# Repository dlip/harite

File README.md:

# Harite 5-way Switch Keyboard

> Harite v2 now released! <https://github.com/dlip/harite-v2>

- 5-way switches - SKRHADE010 rated at 1,000,000 cycles for each direction
- RP2040-Zero controller
- Split using USB-C to connect the halves
- Dual Cirque 40mm trackpads (optional - you can put a Ploopy or other small trackball in place instead)
- QMK Firmware
- Custom PCB and case
- Hot-swapable joystick caps
- The name comes from the Sumo Slap attack in Japanese
- See a [video demonstration](https://youtu.be/vVsztPqckJc)
- If you would like to make your own, checkout the detailed [build guide](build.md)

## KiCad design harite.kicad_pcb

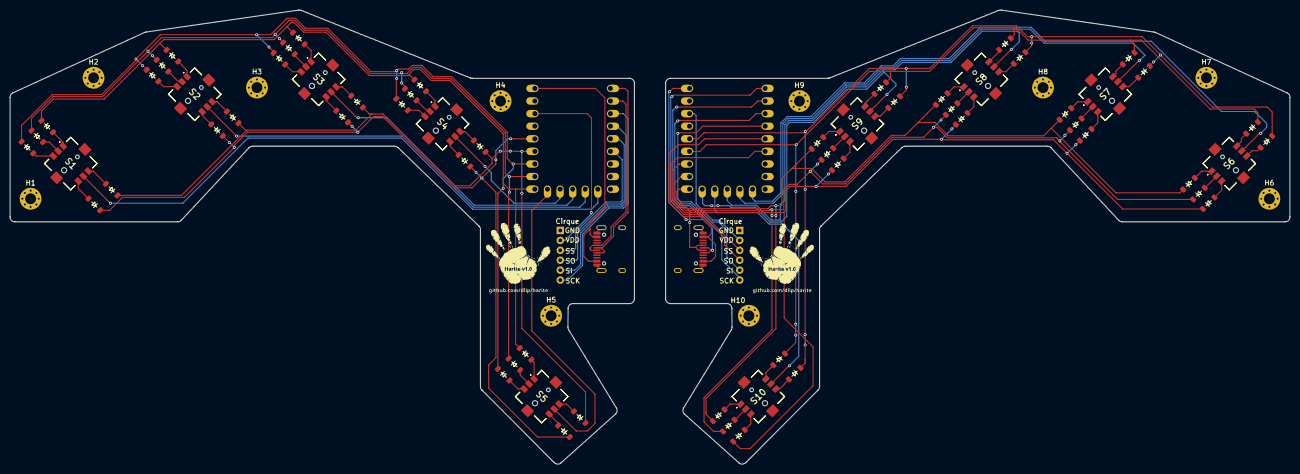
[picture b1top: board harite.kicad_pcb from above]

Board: 2 copper layers, 258.2 x 91.6 mm, 76 parts (0 on the bottom side), 88 nets.

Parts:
D1, D2, D3, D4, D5, D6, D7, D8, D9, D10, D11, D12, D13, D14, D15, D16, D17, D18, D19, D20, D21, D22, D23, D24, D25, D26, D27, D28, D29, D30, D31, D32, D33, D34, D35, D36, D37, D38, D39, D40, D41, D42, D43, D44, D45, D46, D47, D48, D49, D50: D; Diode_SOD-123
H1, H2, H3, H4, H5, H6, H7, H8, H9, H10: Mounting_Hole; MountingHole_2.2mm_M2_Pad_Via
J1, J2: Cirque Connector; Cirque-connector
S1, S2, S3, S4, S5, S6, S7, S8, S9, S10: SKRHADE010; SKRHADE
U1, U2: RP2040_Zero
USB1, USB2: HRO-TYPE-C-31-M-12

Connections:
3V3: J1.2, U1.21 (3V3)
5V: U1.23 (5V), USB1.2 (VBUS), USB1.11 (VBUS)
Col 1: S1.5 (COMMON), U1.10 (9)
Col 2: S2.5 (COMMON), U1.11 (10)
Col 3: S3.5 (COMMON), U1.12 (11)
Col 4: S4.5 (COMMON), U1.13 (12)
Col 5: S5.5 (COMMON), U1.14 (13)
GND: J1.1, U1.22 (GND), USB1.1 (GND), USB1.12 (GND), USB1.13 (SHIELD)
GP0: U1.1 (0), USB1.5 (DN2), USB1.7 (DN1)
GP1: U1.2 (1), USB1.6 (DP1), USB1.8 (DP2)
unnamed: D1.2 (A), S1.1 (A)
unnamed: D2.2 (A), S1.2 (CENTER)
unnamed: D3.2 (A), S1.3 (C)
unnamed: D4.2 (A), S1.4 (B)
unnamed: D5.2 (A), S1.6 (D)
unnamed: D6.2 (A), S2.1 (A)
unnamed: D7.2 (A), S2.2 (CENTER)
unnamed: D8.2 (A), S2.3 (C)
unnamed: D9.2 (A), S2.4 (B)
unnamed: D10.2 (A), S2.6 (D)
unnamed: D11.2 (A), S3.1 (A)
unnamed: D12.2 (A), S3.2 (CENTER)
unnamed: D13.2 (A), S3.3 (C)
unnamed: D14.2 (A), S3.4 (B)
unnamed: D15.2 (A), S3.6 (D)
unnamed: D16.2 (A), S4.1 (A)
unnamed: D17.2 (A), S4.2 (CENTER)
unnamed: D18.2 (A), S4.3 (C)
unnamed: D19.2 (A), S4.4 (B)
unnamed: D20.2 (A), S4.6 (D)
unnamed: D21.2 (A), S5.1 (A)
unnamed: D22.2 (A), S5.2 (CENTER)
unnamed: D23.2 (A), S5.3 (C)
unnamed: D24.2 (A), S5.4 (B)
unnamed: D25.2 (A), S5.6 (D)
unnamed: D26.2 (A), S6.1 (A)
unnamed: D27.2 (A), S6.2 (CENTER)
unnamed: D28.2 (A), S6.3 (C)
unnamed: D29.2 (A), S6.4 (B)
unnamed: D30.2 (A), S6.6 (D)
unnamed: D31.2 (A), S7.1 (A)
unnamed: D32.2 (A), S7.2 (CENTER)
unnamed: D33.2 (A), S7.3 (C)
unnamed: D34.2 (A), S7.4 (B)
unnamed: D35.2 (A), S7.6 (D)
unnamed: D36.2 (A), S8.1 (A)
unnamed: D37.2 (A), S8.2 (CENTER)
unnamed: D38.2 (A), S8.3 (C)
unnamed: D39.2 (A), S8.4 (B)
unnamed: D40.2 (A), S8.6 (D)
unnamed: D41.2 (A), S9.1 (A)
unnamed: D42.2 (A), S9.2 (CENTER)
unnamed: D43.2 (A), S9.3 (C)
unnamed: D44.2 (A), S10.1 (A)
unnamed: D45.2 (A), S10.2 (CENTER)
unnamed: D46.2 (A), S10.3 (C)
unnamed: D47.2 (A), S9.4 (B)
unnamed: D48.2 (A), S9.6 (D)
unnamed: D49.2 (A), S10.4 (B)
unnamed: D50.2 (A), S10.6 (D)
R3V3: J2.2, U2.21 (3V3)
R5V: U2.23 (5V), USB2.2 (VBUS), USB2.11 (VBUS)
RCol 1: S6.5 (COMMON), U2.10 (9)
RCol 2: S7.5 (COMMON), U2.11 (10)
RCol 3: S8.5 (COMMON), U2.12 (11)
RCol 4: S10.5 (COMMON), U2.13 (12)
RCol 5: S9.5 (COMMON), U2.14 (13)
RGND: J2.1, U2.22 (GND), USB2.1 (GND), USB2.12 (GND), USB2.13 (SHIELD)
RGP0: U2.1 (0), USB2.5 (DN2), USB2.7 (DN1)
RGP1: U2.2 (1), USB2.6 (DP1), USB2.8 (DP2)
RRow 1: D26.1 (K), D31.1 (K), D36.1 (K), D41.1 (K), D44.1 (K), U2.15 (14)
RRow 2: D27.1 (K), D32.1 (K), D37.1 (K), D42.1 (K), D45.1 (K), U2.16 (15)
RRow 3: D28.1 (K), D33.1 (K), D38.1 (K), D43.1 (K), D46.1 (K), U2.17 (26)
RRow 4: D29.1 (K), D34.1 (K), D39.1 (K), D47.1 (K), D49.1 (K), U2.18 (27)
RRow 5: D30.1 (K), D35.1 (K), D40.1 (K), D48.1 (K), D50.1 (K), U2.19 (28)
RSCK: J2.6, U2.3 (2)
RSI: J2.5, U2.4 (3)
RSO: J2.4, U2.5 (4)
RSS: J2.3, U2.6 (5)
Row 1: D1.1 (K), D6.1 (K), D11.1 (K), D16.1 (K), D21.1 (K), U1.15 (14)
Row 2: D2.1 (K), D7.1 (K), D12.1 (K), D17.1 (K), D22.1 (K), U1.16 (15)
Row 3: D3.1 (K), D8.1 (K), D13.1 (K), D18.1 (K), D23.1 (K), U1.17 (26)
Row 4: D4.1 (K), D9.1 (K), D14.1 (K), D19.1 (K), D24.1 (K), U1.18 (27)
Row 5: D5.1 (K), D10.1 (K), D15.1 (K), D20.1 (K), D25.1 (K), U1.19 (28)
SCK: J1.6, U1.3 (2)
SI: J1.5, U1.4 (3)
SO: J1.4, U1.5 (4)
SS: J1.3, U1.6 (5)

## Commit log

2024-05-25 Add kicad project
2024-05-25 Start schematic
2024-05-25 Layout switches
2024-05-26 Add scottokeebs
2024-05-26 Add trrs
2024-05-28 Add usbc and cirque
2024-05-28 update usbc
2024-05-28 Fix usb
2024-05-28 Shaping
2024-05-28 Tracks
2024-05-28 Add cirque connector
2024-05-29 Update refs
2024-05-29 cleanup
2024-05-29 mounting holes
2024-05-29 Use skrhade switch model
2024-05-30 Start case
2024-05-30 export board
2024-06-02 Add case files
2024-06-02 Add readme
2024-06-02 Mirror sides
2024-06-02 Organise diodes
2024-06-02 Connect diodes
2024-06-02 Connect the rest
2024-06-02 Fix ground
2024-06-02 Fix diodes
2024-06-02 Track cleanup
2024-06-02 Add gerbers
2024-06-03 Add logo
2024-06-03 Move cirque labels
2024-06-03 Resize logo
2024-06-03 Move diode
2024-06-03 Regen gerbers
2024-06-03 Readme
2024-06-25 move build guide
2024-06-25 build guide
2024-06-25 Change heading
2024-06-25 Build
2024-06-25 Rename
2024-06-25 Add pic
2024-06-25 Add printables
2024-06-26 Update base
2024-06-26 Add main image
2024-06-26 move design
2024-06-26 Add Cirque labels to the back
2024-06-26 Add no cirque case
2024-06-26 Add image
2024-06-28 Add hotswap joysticks
2024-06-28 joystick pics
2024-06-29 Add extra caps
2024-06-29 Add print settings
2024-06-29 Update onshape link
2024-06-29 Add joystick pic
2024-06-29 Update main image
2024-06-29 Update title
2024-06-29 Add youtube link
2024-06-29 Change link
2024-06-30 Improve seat cap
2024-07-18 Add cap details
2024-09-26 Add left/right case files
2024-11-16 Link stained
2024-11-17 Add CC2 Cap
2024-11-17 add xring link
2024-11-24 Revert "add xring link"
    This reverts commit e57f4921604f76ccd5cc1d91443dd8f26f69bd96.
2024-11-24 Revert "Add CC2 Cap"
    This reverts commit 0095e71b417e125be702f3604542a93561a7ed3b.
2024-11-25 Add xring
2024-11-26 Improve xring with some plier buffer to protect the rim
2024-12-17 Change xring diameter
2025-01-11 Add v2 link
